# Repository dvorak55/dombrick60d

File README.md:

# dombrick60d : Dvorak Oriented 60% Keyboard dedicated to Dell

Dombrick60D is self made dvorak oriented keyboard.  
Dombrick60DはDvorak配列志向の自作キーボードです。

"Dombrick" stands for Dvorak Oriented Mechanical Breakthough Remakable Interesting Coolest Keyboard (joke  
Dombrickという名前は「Dvorak志向の革新的で驚くべき大変興味深い最高にクールな機械式キーボード」を表す英単語の頭文字を取って命名しました（笑

Actually, "Dombri" means one of a japanese food style bowl, "ck" means nothing.  
嘘です、Dombriはもちろん日本語の丼を意味しており、ckの二文字はバランスを整えるために付けているだけです。

以下、[DescriptionのPDF](https://github.com/dvorak55/dombrick60d/blob/master/description.pdf)から抜粋

## 概要
Dombrick60DはDvorak配列志向の45%キーボードDombrick45にDellのノートパソコンで採用されていたカーソルキー／PGUP／PGDWを追加、かつマクロ用Chocキーを手前に配置した変態配列キーボードです。

## 特徴
- 横幅14.75U。相変わらずDvorak配列ユーザ志向のキーマップ
- 数字キーが無いのに60%キーボードを名乗る図々しさ
- +と=キーを本来の位置に搭載、カーソルキーもあの位置に搭載
- 最下段の下段(?)にマクロ・ショートカット用のキーを10個搭載
- 一応6.25uスペースバーも選べる(けど作者は使いません)
- モビロンバンドとシリコンマットによるマウント方式は健在だよ! • (最下段の下段以外は)一般的なキーキャップに対応
- DellのPCが使いたくなるPCBシルクデザイン(ロゴを入れただけ)

## キー配列

最下段のさらに下段（？）の10キーはChoc。Chocなのでスペースキーを押す時に干渉しない、はずなんです。

## Kitに入っている部品
1. PCB 1枚
2. 電子部品(コンデンサ 6個、ダイオード 65個、フューズ 1個、抵抗 6個、ESDダイオード 1個、水晶振動子 1個、リセットスイッチ 1個)
3. MCU(ATmega32U2 1個)
4. USB端子(USB-C 1個)
5. スタビライザー(2Uと6.25Uがそれぞれ 1個ずつ)
6. モビロンゴム(55mm 12本、100mm 6本)
7. シリコンシート(基板サイズ 2枚分)
8. ボトムプレート(厚さ1.5mmステンレス 1枚)

## 別途ご用意頂く部品
1. キースイッチ(Cherry MX互換で5ピンPCBマウント) 53個
2. キースイッチ(Choc) 10個
3. キーキャップ(Cherry MX互換 53個、Choc 10個)
4. USB-Cケーブル

## スペック（実装例）
サイズ：77mm × 253mm × 23mm

重さ　：約560グラム

## スイッチ互換性
Cherry MX互換とALPS(ただし最下段 の下段キーはChoc)

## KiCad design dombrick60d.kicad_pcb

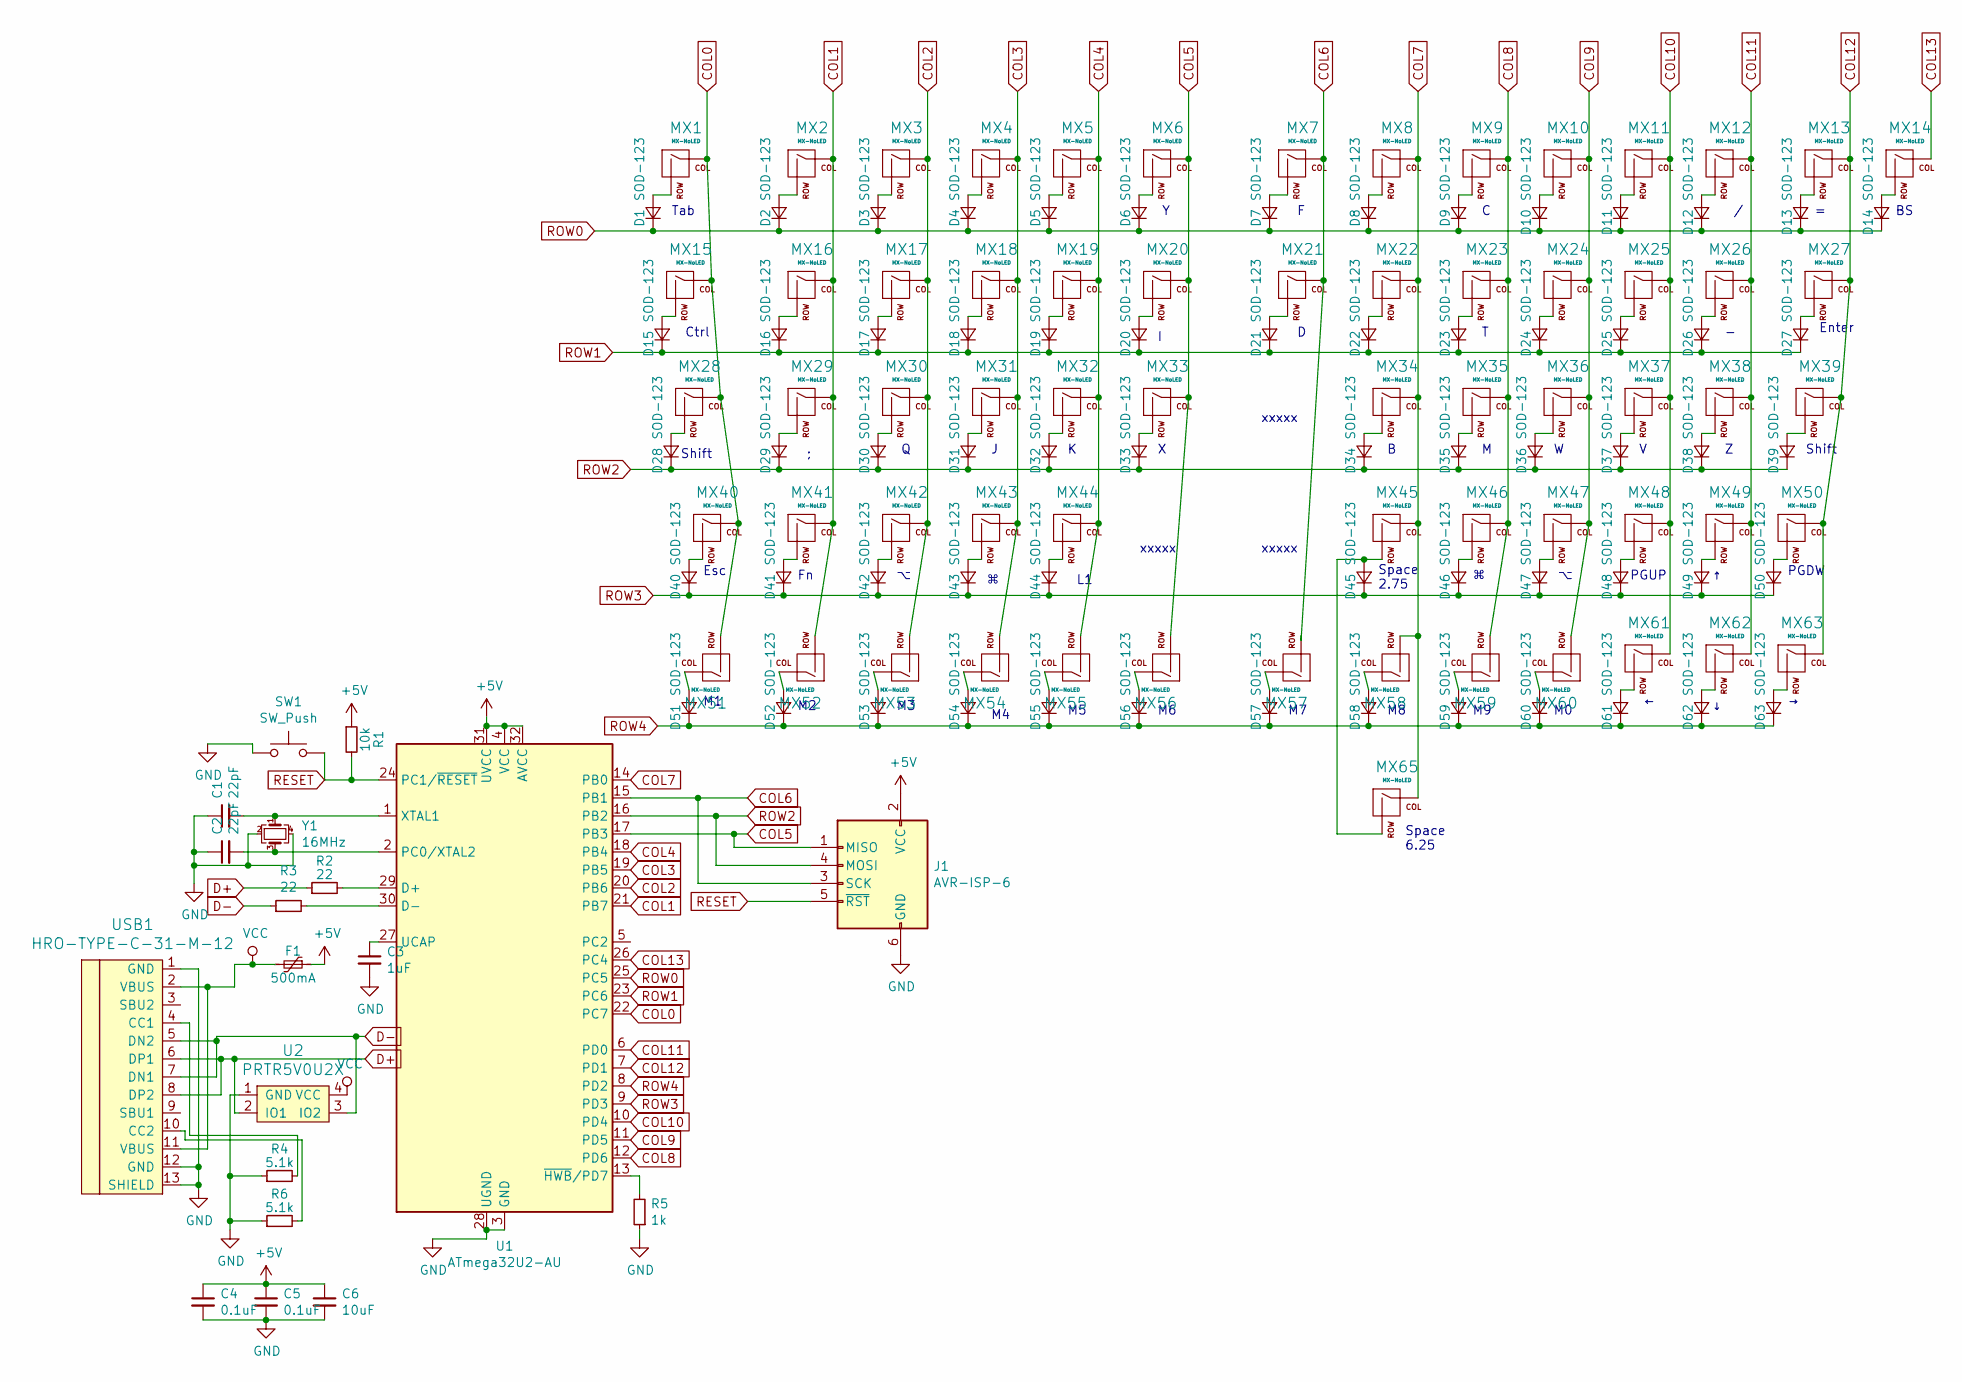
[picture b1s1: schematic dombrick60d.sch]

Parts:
C1, C2: 22pF; C_0805_2012Metric_Pad1.15x1.40mm_HandSolder
C3: 1uF; C_0805_2012Metric_Pad1.15x1.40mm_HandSolder
C4, C5: 0.1uF; C_0805_2012Metric_Pad1.15x1.40mm_HandSolder
C6: 10uF; C_0805_2012Metric_Pad1.15x1.40mm_HandSolder
D1, D2, D3, D4, D5, D6, D7, D8, D9, D10, D11, D12, D13, D14, D15, D16, D17, D18, D19, D20, D21, D22, D23, D24, D25, D26, D27, D28, D29, D30, D31, D32, D33, D34, D35, D36, D37, D38, D39, D40, D41, D42, D43, D44, D45, D46, D47, D48, D49, D50, D51, D52, D53, D54, D55, D56, D57, D58, D59, D60, D61, D62, D63: SOD-123; D_SOD-123
F1: 500mA; Fuse_1206_3216Metric_Pad1.42x1.75mm_HandSolder
J1: AVR-ISP-6; Reset_Pretty
MX1: MX-NoLED; MX-1.5U-NoLED
MX2, MX3, MX4, MX5, MX6, MX7, MX8, MX9, MX10, MX11, MX12, MX13, MX14, MX16, MX17, MX18, MX19, MX20, MX21, MX22, MX23, MX24, MX25, MX26, MX29, MX30, MX31, MX32, MX33, MX34, MX35, MX36, MX37, MX38, MX40, MX41, MX42, MX48, MX49, MX50, MX61, MX62, MX63: MX-NoLED; MX-1U-NoLED
MX15, MX27: MX-NoLED; MX-1.75U-NoLED
MX28, MX39, MX44: MX-NoLED; MX-2.25U-NoLED
MX43, MX46, MX47: MX-NoLED; MX-1.25U-NoLED
MX45: MX-NoLED; MX-2.75U-NoLED
MX51, MX52, MX53, MX54, MX55, MX56, MX57, MX58, MX59, MX60: MX-NoLED; KailhChoc-1U
MX65: MX-NoLED; MX-6.25U-NoLED
R1: 10k; R_0805_2012Metric
R2, R3: 22; R_0805_2012Metric
R4, R6: 5.1k; R_0805_2012Metric
R5: 1k; R_0805_2012Metric
SW1: SW_Push; SKQG-1155865
U1: ATmega32U2-AU; TQFP-32_7x7mm_P0.8mm
U2: PRTR5V0U2X; SOT143B
USB1: HRO-TYPE-C-31-M-12; HRO-TYPE-C-31-M-12-Assembly
Y1: 16MHz; Crystal_SMD_3225-4Pin_3.2x2.5mm

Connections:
+5V: C4.1, C5.1, C6.1, F1.1, J1.2 (VCC), R1.1, U1.4 (VCC), U1.31 (UVCC), U1.32 (AVCC)
COL0: MX1.1 (COL), MX15.1 (COL), MX28.1 (COL), MX40.1 (COL), MX51.2 (ROW), U1.22 (PC7)
COL1: MX2.1 (COL), MX16.1 (COL), MX29.1 (COL), MX41.1 (COL), MX52.2 (ROW), U1.21 (PB7)
COL2: MX3.1 (COL), MX17.1 (COL), MX30.1 (COL), MX42.1 (COL), MX53.2 (ROW), U1.20 (PB6)
COL3: MX4.1 (COL), MX18.1 (COL), MX31.1 (COL), MX43.1 (COL), MX54.2 (ROW), U1.19 (PB5)
COL4: MX5.1 (COL), MX19.1 (COL), MX32.1 (COL), MX44.1 (COL), MX55.2 (ROW), U1.18 (PB4)
COL5: J1.1 (MISO), MX6.1 (COL), MX20.1 (COL), MX33.1 (COL), MX56.2 (ROW), U1.17 (PB3)
COL6: J1.3 (SCK), MX7.1 (COL), MX21.1 (COL), MX57.2 (ROW), U1.15 (PB1)
COL7: MX8.1 (COL), MX22.1 (COL), MX34.1 (COL), MX45.1 (COL), MX58.2 (ROW), MX65.1 (COL), U1.14 (PB0)
COL8: MX9.1 (COL), MX23.1 (COL), MX35.1 (COL), MX46.1 (COL), MX59.2 (ROW), U1.12 (PD6)
COL9: MX10.1 (COL), MX24.1 (COL), MX36.1 (COL), MX47.1 (COL), MX60.2 (ROW), U1.11 (PD5)
COL10: MX11.1 (COL), MX25.1 (COL), MX37.1 (COL), MX48.1 (COL), MX61.1 (COL), U1.10 (PD4)
COL11: MX12.1 (COL), MX26.1 (COL), MX38.1 (COL), MX49.1 (COL), MX62.1 (COL), U1.6 (PD0)
COL12: MX13.1 (COL), MX27.1 (COL), MX39.1 (COL), MX50.1 (COL), MX63.1 (COL), U1.7 (PD1)
COL13: MX14.1 (COL), U1.26 (PC4)
D+: R2.1, U2.2 (IO1), USB1.6 (DP1), USB1.8 (DP2)
D-: R3.1, U2.3 (IO2), USB1.5 (DN2), USB1.7 (DN1)
GND: C1.1, C2.1, C3.2, C4.2, C5.2, C6.2, J1.6 (GND), R4.1, R5.1, R6.1, SW1.1, U1.3 (GND), U1.28 (UGND), U2.1 (GND), USB1.1 (GND), USB1.12 (GND), USB1.13 (SHIELD), Y1.2, Y1.4
unnamed: C1.2, U1.1 (XTAL1), Y1.1
unnamed: C2.2, U1.2 (PC0/XTAL2), Y1.3
unnamed: C3.1, U1.27 (UCAP)
unnamed: D1.2 (A), MX1.2 (ROW)
unnamed: D2.2 (A), MX2.2 (ROW)
unnamed: D3.2 (A), MX3.2 (ROW)
unnamed: D4.2 (A), MX4.2 (ROW)
unnamed: D5.2 (A), MX5.2 (ROW)
unnamed: D6.2 (A), MX6.2 (ROW)
unnamed: D7.2 (A), MX7.2 (ROW)
unnamed: D8.2 (A), MX8.2 (ROW)
unnamed: D9.2 (A), MX9.2 (ROW)
unnamed: D10.2 (A), MX10.2 (ROW)
unnamed: D11.2 (A), MX11.2 (ROW)
unnamed: D12.2 (A), MX12.2 (ROW)
unnamed: D13.2 (A), MX13.2 (ROW)
unnamed: D14.2 (A), MX14.2 (ROW)
unnamed: D15.2 (A), MX15.2 (ROW)
unnamed: D16.2 (A), MX16.2 (ROW)
unnamed: D17.2 (A), MX17.2 (ROW)
unnamed: D18.2 (A), MX18.2 (ROW)
unnamed: D19.2 (A), MX19.2 (ROW)
unnamed: D20.2 (A), MX20.2 (ROW)
unnamed: D21.2 (A), MX21.2 (ROW)
unnamed: D22.2 (A), MX22.2 (ROW)
unnamed: D23.2 (A), MX23.2 (ROW)
unnamed: D24.2 (A), MX24.2 (ROW)
unnamed: D25.2 (A), MX25.2 (ROW)
unnamed: D26.2 (A), MX26.2 (ROW)
unnamed: D27.2 (A), MX27.2 (ROW)
unnamed: D28.2 (A), MX28.2 (ROW)
unnamed: D29.2 (A), MX29.2 (ROW)
unnamed: D30.2 (A), MX30.2 (ROW)
unnamed: D31.2 (A), MX31.2 (ROW)
unnamed: D32.2 (A), MX32.2 (ROW)
unnamed: D33.2 (A), MX33.2 (ROW)
unnamed: D34.2 (A), MX34.2 (ROW)
unnamed: D35.2 (A), MX35.2 (ROW)
unnamed: D36.2 (A), MX36.2 (ROW)
unnamed: D37.2 (A), MX37.2 (ROW)
unnamed: D38.2 (A), MX38.2 (ROW)
unnamed: D39.2 (A), MX39.2 (ROW)
unnamed: D40.2 (A), MX40.2 (ROW)
unnamed: D41.2 (A), MX41.2 (ROW)
unnamed: D42.2 (A), MX42.2 (ROW)
unnamed: D43.2 (A), MX43.2 (ROW)
unnamed: D44.2 (A), MX44.2 (ROW)
unnamed: D45.2 (A), MX45.2 (ROW), MX65.2 (ROW)
unnamed: D46.2 (A), MX46.2 (ROW)
unnamed: D47.2 (A), MX47.2 (ROW)
unnamed: D48.2 (A), MX48.2 (ROW)
unnamed: D49.2 (A), MX49.2 (ROW)
unnamed: D50.2 (A), MX50.2 (ROW)
unnamed: D51.2 (A), MX51.1 (COL)
unnamed: D52.2 (A), MX52.1 (COL)
unnamed: D53.2 (A), MX53.1 (COL)
unnamed: D54.2 (A), MX54.1 (COL)
unnamed: D55.2 (A), MX55.1 (COL)
unnamed: D56.2 (A), MX56.1 (COL)
unnamed: D57.2 (A), MX57.1 (COL)
unnamed: D58.2 (A), MX58.1 (COL)
unnamed: D59.2 (A), MX59.1 (COL)
unnamed: D60.2 (A), MX60.1 (COL)
unnamed: D61.2 (A), MX61.2 (ROW)
unnamed: D62.2 (A), MX62.2 (ROW)
unnamed: D63.2 (A), MX63.2 (ROW)
unnamed: R2.2, U1.29 (D+)
unnamed: R3.2, U1.30 (D-)
unnamed: R4.2, USB1.4 (CC1)
unnamed: R5.2, U1.13 (~HWB~/PD7)
unnamed: R6.2, USB1.10 (CC2)
RESET: J1.5 (~RST), R1.2, SW1.2, U1.24 (PC1/~RESET)
ROW0: D1.1 (K), D2.1 (K), D3.1 (K), D4.1 (K), D5.1 (K), D6.1 (K), D7.1 (K), D8.1 (K), D9.1 (K), D10.1 (K), D11.1 (K), D12.1 (K), D13.1 (K), D14.1 (K), U1.25 (PC5)
ROW1: D15.1 (K), D16.1 (K), D17.1 (K), D18.1 (K), D19.1 (K), D20.1 (K), D21.1 (K), D22.1 (K), D23.1 (K), D24.1 (K), D25.1 (K), D26.1 (K), D27.1 (K), U1.23 (PC6)
ROW2: D28.1 (K), D29.1 (K), D30.1 (K), D31.1 (K), D32.1 (K), D33.1 (K), D34.1 (K), D35.1 (K), D36.1 (K), D37.1 (K), D38.1 (K), D39.1 (K), J1.4 (MOSI), U1.16 (PB2)
ROW3: D40.1 (K), D41.1 (K), D42.1 (K), D43.1 (K), D44.1 (K), D45.1 (K), D46.1 (K), D47.1 (K), D48.1 (K), D49.1 (K), D50.1 (K), U1.9 (PD3)
ROW4: D51.1 (K), D52.1 (K), D53.1 (K), D54.1 (K), D55.1 (K), D56.1 (K), D57.1 (K), D58.1 (K), D59.1 (K), D60.1 (K), D61.1 (K), D62.1 (K), D63.1 (K), U1.8 (PD2)
VCC: F1.2, U2.4 (VCC), USB1.2 (VBUS), USB1.11 (VBUS)

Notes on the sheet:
Space 2.75
PGDW
Enter
Tab
Esc
Shift
Ctrl
PGUP
xxxxx
Space 6.25

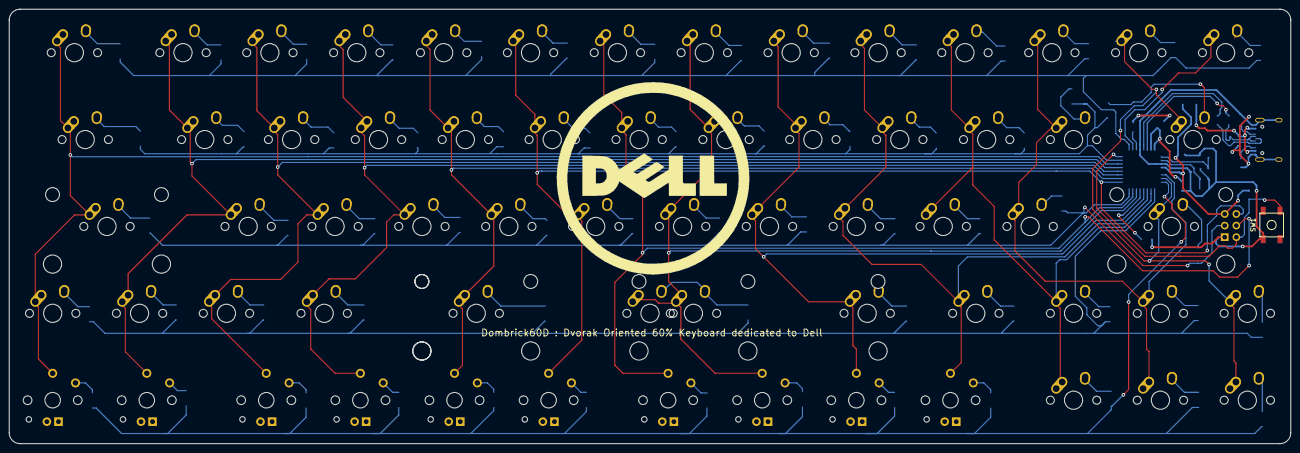
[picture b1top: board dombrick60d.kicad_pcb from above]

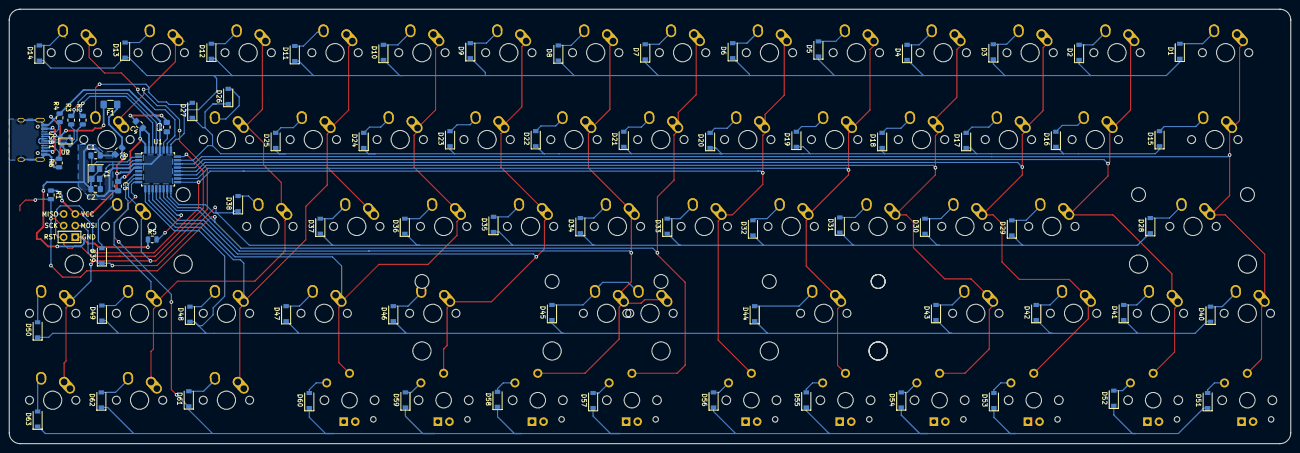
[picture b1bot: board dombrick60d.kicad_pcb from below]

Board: 2 copper layers, 281.0 x 95.3 mm, 146 parts (81 on the bottom side), 96 nets.

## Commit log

2020-01-14 create kicad pro
2020-01-14 add submodule of ai03god
2020-01-14 Add footprint libraries
2020-01-15 Add usb-c submodules
2020-01-15 add usb-c footprint libraries
2020-01-15 sch tabun done
2020-01-15 sugee ganbatta
2020-01-18 sugoku ganbatta
2020-01-18 pcb haisen ok
2020-01-18 2020-01-19 all ok lets production start
2020-01-18 gerber generate done
2020-01-28 2020年1月29日
    logo toka tuika shita
2020-01-30 create readme.md
    DELLに怒られたらどうしようと怯えるようでは駄目
2020-01-30 add keymap picture
2020-02-14 2020-02-15 dombrick60d finish!!
    Dombrick60Dが完成しました。
    嬉しい。
2020-03-22 keymap updaet
